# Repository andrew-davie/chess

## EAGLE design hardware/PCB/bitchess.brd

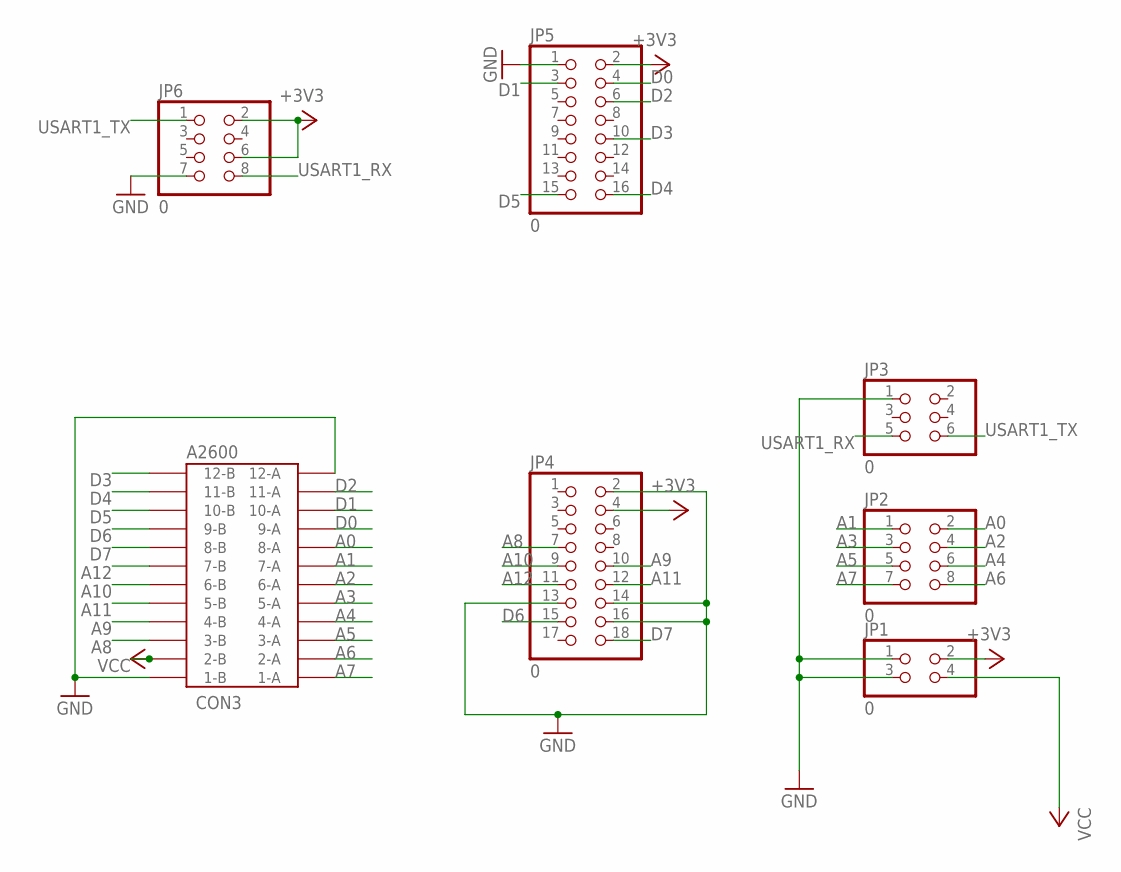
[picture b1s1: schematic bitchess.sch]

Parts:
CON3: A2600; 24PINEDGE-254MM
JP1: 0; 2X02
JP2, JP6: 0; 2X04
JP3: 0; 2X03
JP4: 0; 2X09
JP5: 0; 2X08

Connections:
+3V3: JP1.2, JP4.4, JP5.2, JP6.2, JP6.6
A0: CON3.8-A, JP2.2
A1: CON3.7-A, JP2.1
A2: CON3.6-A, JP2.4
A3: CON3.5-A, JP2.3
A4: CON3.4-A, JP2.6
A5: CON3.3-A, JP2.5
A6: CON3.2-A, JP2.8
A7: CON3.1-A, JP2.7
A8: CON3.3-B, JP4.7
A9: CON3.4-B, JP4.10
A10: CON3.6-B, JP4.9
A11: CON3.5-B, JP4.12
A12: CON3.7-B, JP4.11
D0: CON3.9-A, JP5.4
D1: CON3.10-A, JP5.3
D2: CON3.11-A, JP5.6
D3: CON3.12-B, JP5.10
D4: CON3.11-B, JP5.16
D5: CON3.10-B, JP5.15
D6: CON3.9-B, JP4.15
D7: CON3.8-B, JP4.18
GND: CON3.1-B, CON3.12-A, JP1.1, JP1.3, JP3.1, JP4.2, JP4.13, JP4.14, JP4.16, JP5.1, JP6.7
USART1_RX: JP3.5, JP6.8
USART1_TX: JP3.6, JP6.1
VCC: CON3.2-B, JP1.4

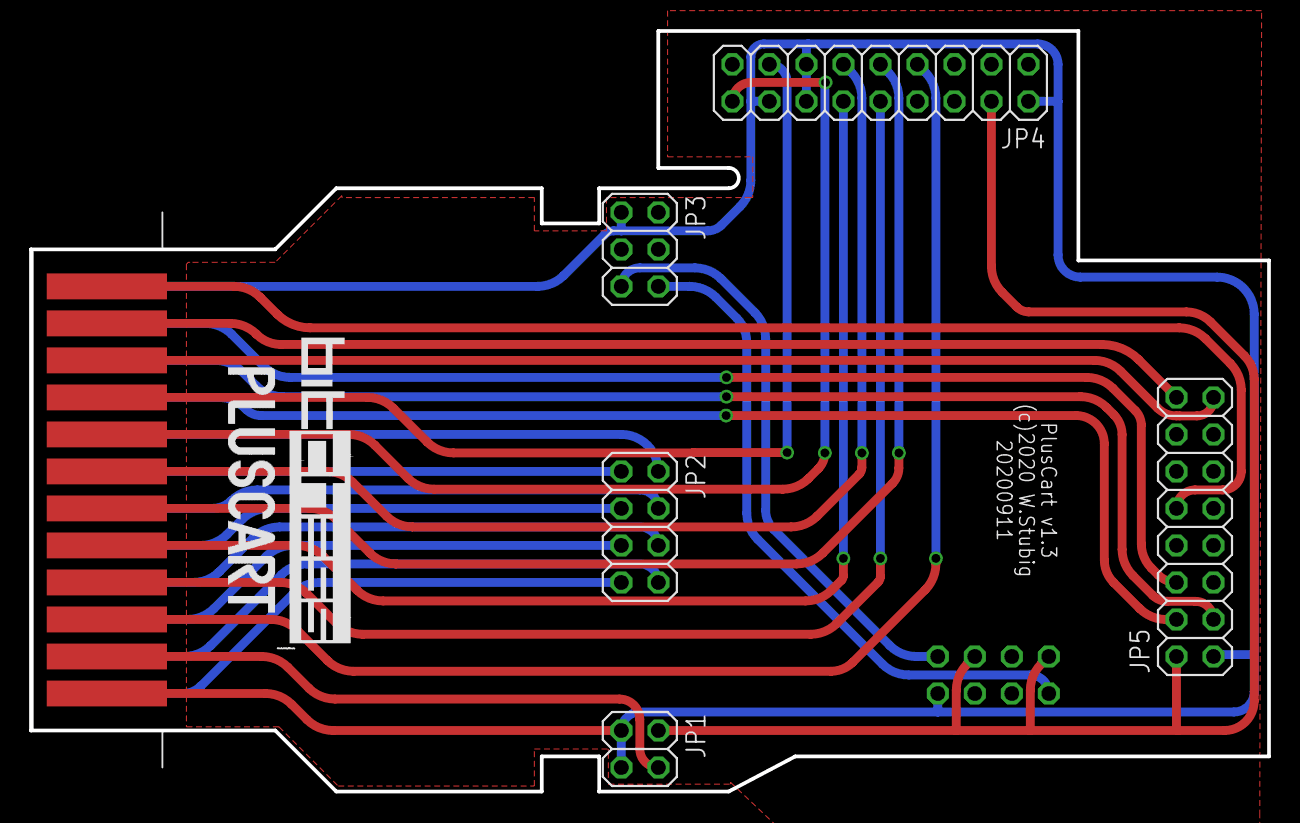
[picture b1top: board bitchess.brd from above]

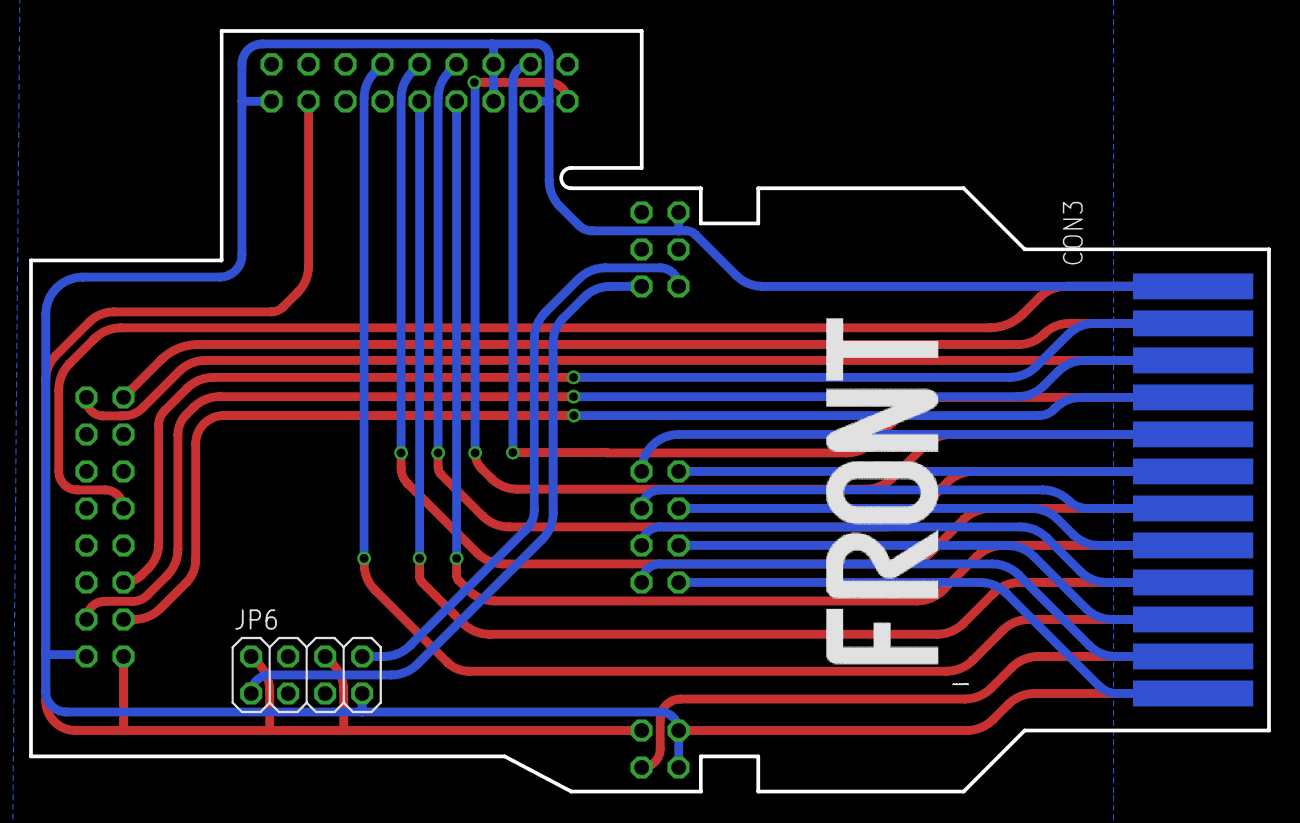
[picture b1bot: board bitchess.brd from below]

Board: 2 copper layers, 85.0 x 52.2 mm, 7 parts (2 on the bottom side), 26 nets.

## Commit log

2020-01-11 first bitmap draw (non-mockup)
2020-01-12 board draw complete. random piece moves
2020-01-13 eor draw completed
2020-01-14 eor move more work
2020-01-15 good eor draw
2020-01-21 beginning of move generatino
2020-01-23 move code written for all piece types split pawns to wpawn and bpawn ram banks for move handlers automated RAMBANK_ naming for subroutines
2020-01-25 merged into 10x12 representation
2020-01-28 pawn promotion working still a random crash after a long play
2020-01-28 test
2020-01-29 two player movement B pawn +2 disabled/bug flashing at end of move
2020-02-01 optimisations
2020-02-03 new board initialisation with piecelist + sorted piecelist. Still ending up with error board after moves, though. Bug there somewhere!
    Started putting sprite on row intended for move selection by player.
2020-02-15 continuing UI improvements cancel move added still need to fix castling, en-passant
2020-02-16 fixed bug on "castle" single square king move
2020-02-20 removed 2nd state machine, now everything is running inside the AIStateMachine fixed UI responsiveness by actioning on button/joystick as soon as possible
2020-02-24 pawn promotion
2020-02-26 new auto-generated state lo/hi tables chasing PIECE_MASK bug on fromPiece pawn promotion working
2020-03-09 refactoring FIXED slow work. tired.
2020-03-11 removed all base64 dependencies now all X12
2020-03-15 fixed enpassant. finally?
2020-03-16 optimising
2020-03-24 after speech, prior to alphabeta call
2020-04-04 first real gameplay
2020-04-08 sorting
2020-04-12 pawn promotino OK
2020-04-14 negamax search rewrite!
2020-04-15 about to start check for check stuff
2020-04-18 gorgeous with quiescence #2
2020-04-27 thinkbars, check removed from searching
2020-04-29 5 ply starting enpassant stuff too
2020-05-07 3E+ screen draw working
2020-05-07 just before move generation
2020-05-09 halfway there
2020-05-12 first working 3E+ - no quiescence or castling
2020-05-13 negamax seems ok but fails with quiesce added
2020-05-15 bug slain
2020-05-16 promotion fixed (white) black unkonwn
2020-05-17 castling across check, pawn promotion
2020-06-11 now 3e+ compatible (startup slot!=0)
2020-06-12 pottering
2020-06-24 started message windows
2020-07-16 castling fixed and a whole lot of stuff
2020-07-22 move eval added
2020-07-25 prelim recursive sorte
2020-07-30 new sort, but kludgy
2020-08-12 sort disabled
2020-09-08 long time no update
2020-09-10 cleaning out the rubbish
2020-09-10 more trash removed
2020-09-10 more cleanup added hardware - 3D files and PCB layout random board draw proto
2020-09-10 added gerber files for PCB - ready to have manufactured!
2020-09-11 randomised board. gcode.
2022-01-17 cleanup
2025-12-31 no idea if this is OK, but committing to tidy up

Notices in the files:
hardware/PCB/bitchess.brd:
(c)2020 W.Stubig
